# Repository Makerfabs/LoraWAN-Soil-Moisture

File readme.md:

# LoraWAN Soil Moisture

```c++
/*
Version:		V1.2
Author:			Vincent
Create Date:	2022/12/15
Note:
	2022/12/30	V1.2	:Update readme
	2022/12/16 	V1.1	:Fix adc3 read error.
*/
```

[toc]

# Makerfabs

[Makerfabs home page](https://www.makerfabs.com/)

[Makerfabs Wiki](https://wiki.makerfabs.com/)

# LoraWAN Soil Moisture
## Intruduce

Product Link ：[LoRaWAN Temperature/ Humidity/ Soil Moisture Sensor](https://www.makerfabs.com/lorawan-temperatur-humidity-soil-moisture-sensor.html) 

Wiki Link : [LoRaWAN Temperature/ Humidity Soil Moisture Sensor](https://wiki.makerfabs.com/LoRaWAN_Temperature_Humidity_Soil_Moisture_Sensor.html) 

This module monitor soil moisture via capacitive method, with waterproof coating, it avoids the corrosion problem that usually happens on cheap resistor-mode soil moisture sensor. There is also onboard AHT10 -air temperature/ humidity sensor, to monitor air status, proper for usage in the greenhouse. This module uses 3x AAA battery as power, with sleep current of 26uA and working current of 4mA, the average working time can be more than 1 year. (with 1-hour message interval, Class A ).

## Feature

- LoRaWAN Nodes, RA08H
- Soil Moisture Measurement based on capacitive Testing
- Low power: 7.1uA when sleeping/4mA in message sending turn around
- Onboard AHT10 sensor to monitor air temperature and air humidity
- Onboard Battery Voltage Measurement
- Full Open Source- all hardware and software open at GitHub
- Compatible with Arduino
- Supply power voltage: 4.7~3.5V

### Front:

### Back:

# Code

## Compiler Options

**If you have any questions，such as how to install the development board, how to download the code, how to install the library. Please refer to :[Makerfabs_FAQ](https://github.com/Makerfabs/Makerfabs_FAQ)**

- Open code with Arduino IDE
- Set Lorawan config in code.
- Upload codes, select "Arduino Pro or Pro Mini" and "3.3V 8MHz"

## Uploader

There is no USB socket or integrated serial port chip on some modules. But there are serial ports: VCC, GND, RX, TX, DTR. 

There are two ways to connect a serial port.

### MakerFabs CP2104 USB2UART

Product link : [CP2104 USB2UART](https://www.makerfabs.com/cp2104-usb-to-serial-converter.html)

This CP2104 USB to Serial Converter is super tiny, a highly-integrated USB-to-UART Bridge Controller providing a simple solution for updating and programming.

The serial port module has the same pin position as the makerfabs module with no USB port. So just plug it into the hole.

The usage of usb cable is the same after that.

### CP2102 MODULES USB TO TTL

There are many common USB serial port modules on the market, which are basically connected in a common way.

| Makerfabs | USB To TTL |
| --------- | ---------- |
| VCC       | 3.3V       |
| GND       | GND        |
| RX        | TXD        |
| TX        | RXD        |

## Testing file for manufacture

**moisture_test.ino**

This is a test demo. You can check all sensor, button, led and Lorawan.

Change Lorawan config to yourself.

```c++
//config.h

#define DEVEUI "YOUR_DEVEUI"
#define APPEUI "YOUR_APPEUI"
#define APPKEY "YOUR_APPKEY"

```

When hold on button, will send lorawan message to TTN.

```c++

```

## Firmware Frame

**mositure_lorawan**

This routine is expected to run on 3 AAA batteries for a year (once per hour).

Hibernation current 26ua, normal working current 4.7ma, peak emission 8.7ma.

The register is used to read the soil ADC and the battery voltage ADC. 

~~*There is a bug in the battery voltage ADC reading at present and it is being modified.*~~

Change Lorawan config to yourself.

Set sleep time, every watchdog sleep cycle nearly 8.5 s.

```c++
//Almost 1 hours
#define SLEEP_CYCLE 450
```

Lorawan sends data in the following ways:

```c++
    String temp = "AT+DTRX=1,2,8,";

    char data_str[80];
    sprintf(data_str, "%02x%02x%02x%02x", 
            (int)temperature, (int)humidity, soil_percent, bat_vol);
    temp = temp + data_str;
```

The corresponding parsing function for the thing network is as follows:

```javascript
function decodeUplink(input) {
  
  var temp = input.bytes[0]
  var humi = input.bytes[1]
  var adc = input.bytes[2]*256+input.bytes[3]
  var bat = input.bytes[4]/10
  var num = input.bytes[5] * 100 + input.bytes[6] 
  
  return {
    data:{
    //adc,
    //temp,
    //humi,
    //bat,
    //num,
    field1:adc,
    field2:temp,
    field3:humi,
    field4:bat,
    field5:num,
    },
    
  };
  
```

## Example

### 328p_at

Example for AT command test.

### adc_sleep

Tests whether ADC reads normally after MCU sleeps.

# Case

3D print case

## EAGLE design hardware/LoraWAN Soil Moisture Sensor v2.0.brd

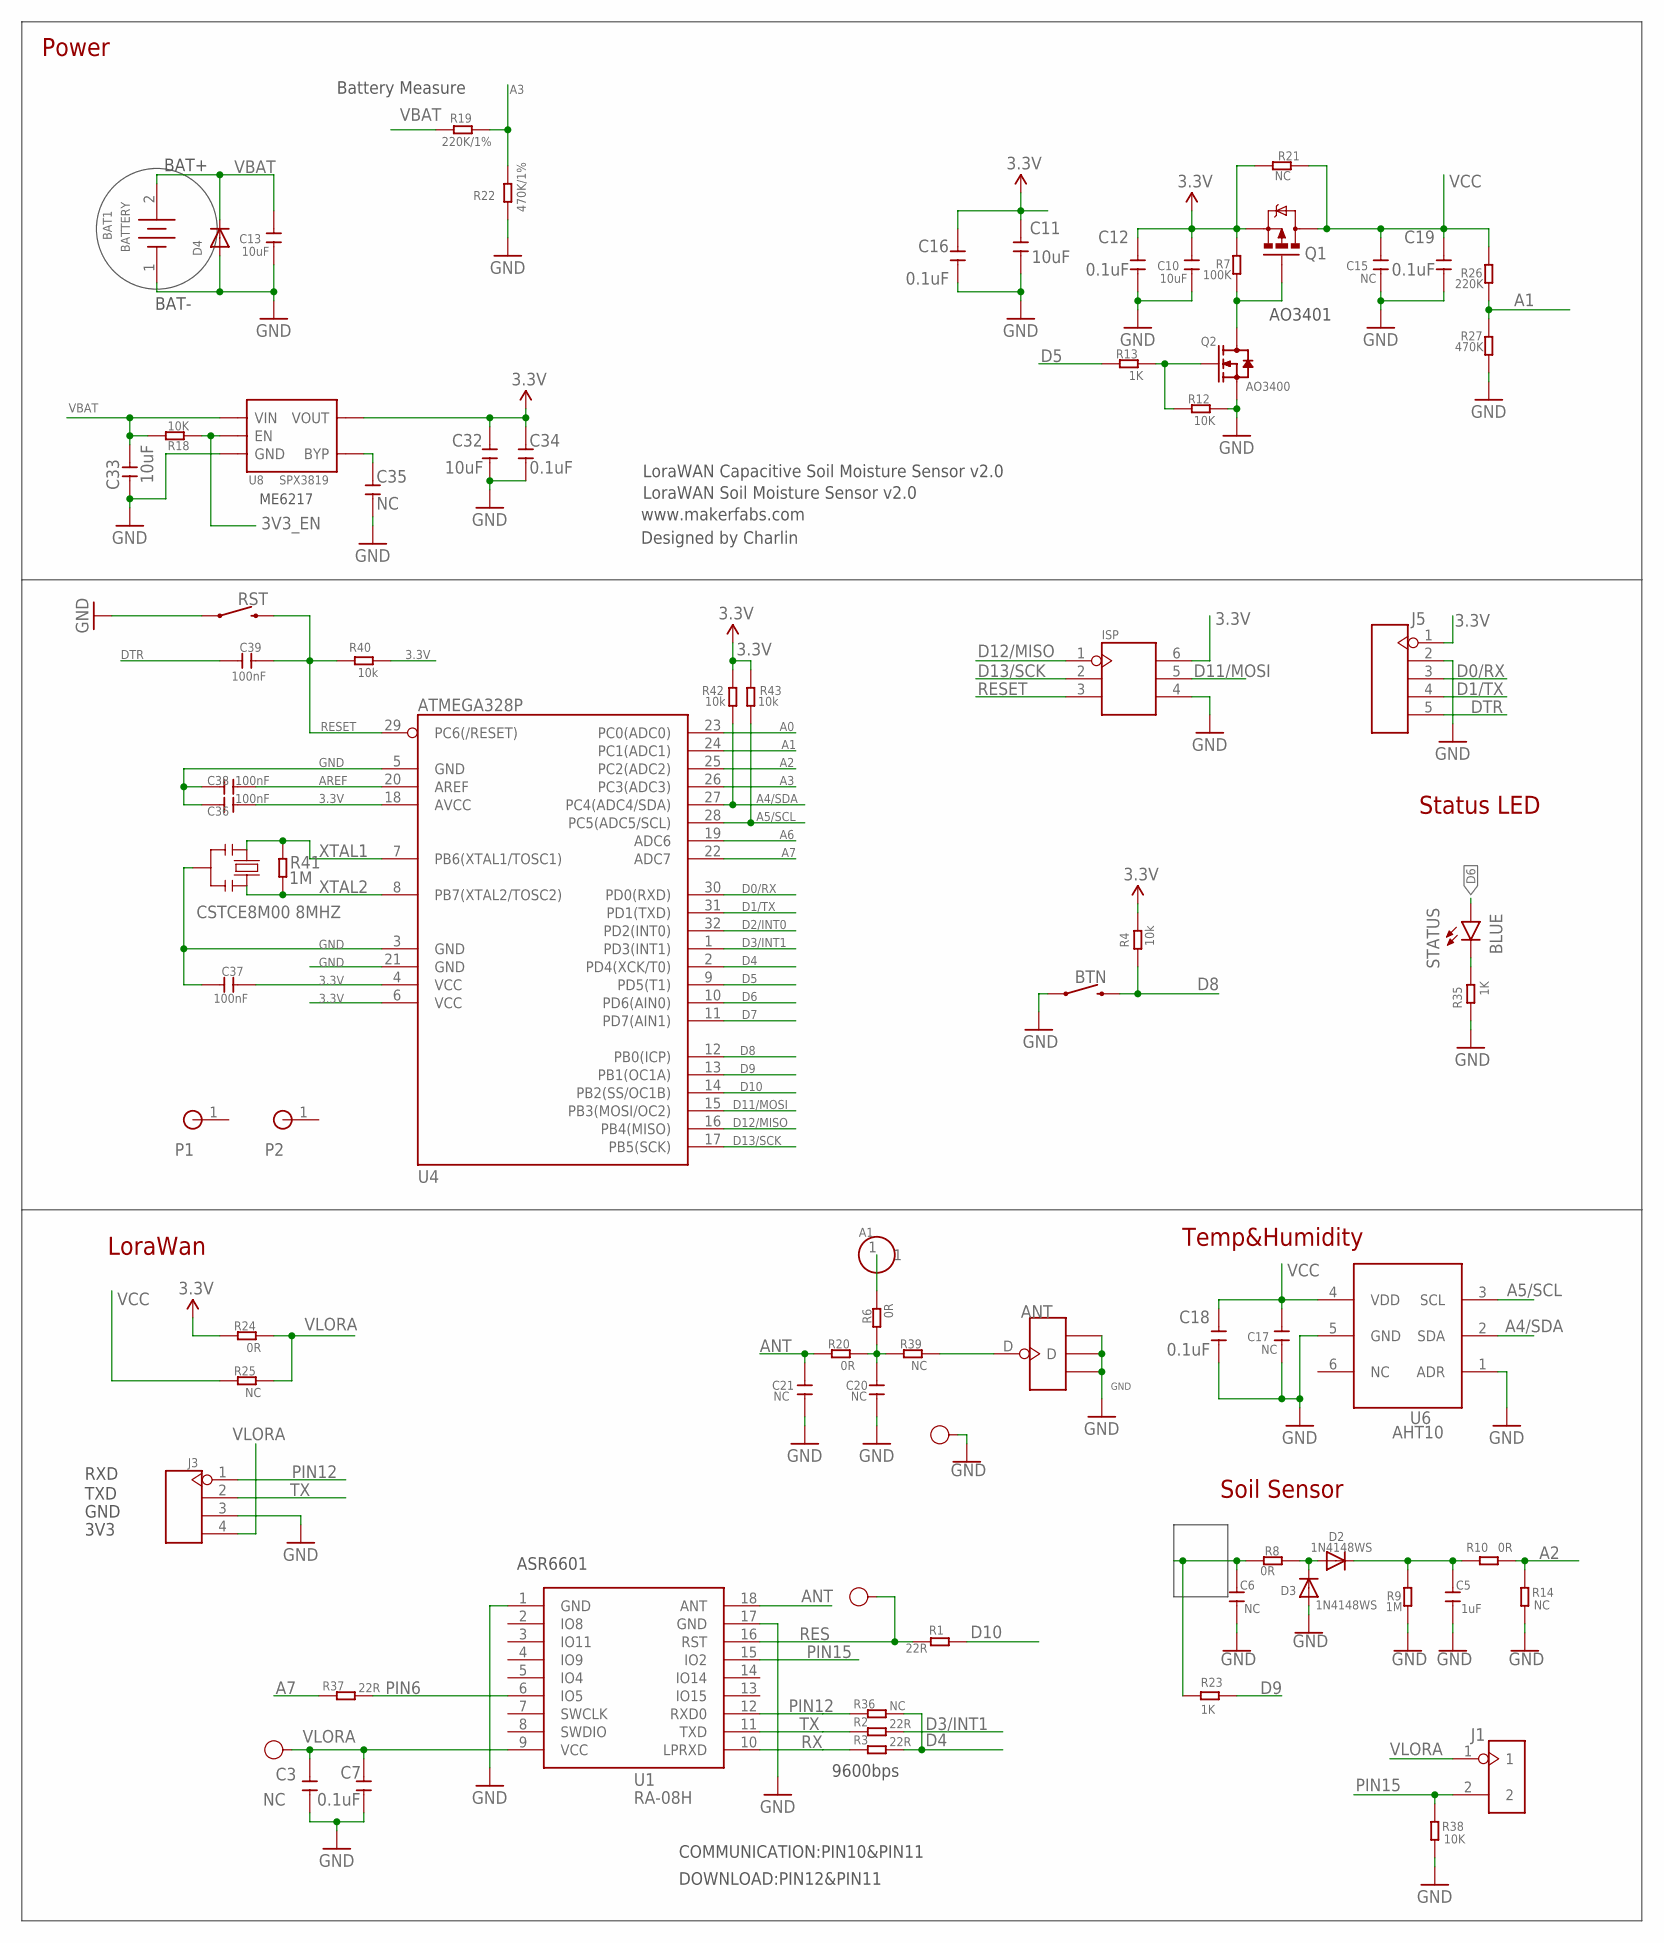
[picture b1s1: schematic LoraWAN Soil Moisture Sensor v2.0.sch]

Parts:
3V3: TEST-POINT'4545'; TP-D45MIL; PARTNO DNP
A1: HEADER-1P-50; 1P-100/50MIL
ANT: ANTENNA-U-FL; 4P-U-FL
BAT1: BATTERY
BTN: MOMENTARY-SWITCH-SPST-SMD-6.0X3.5MM; TACTILE_SWITCH_SMD_6.0X3.5MM
C3, C15, C17, C20, C21, C35: NC; 0603
C5: 1uF; DISCRETE_C0603
C6: NC; DISCRETE_C0603
C7, C12, C16, C18, C19, C34: 0.1uF; 0603
C10, C11, C13, C32, C33: 10uF; 0603
C36, C37, C38, C39: 100nF; 0603
D2, D3: 1N4148WS; SOD-323F
D4: DIODESOD-323F; SOD-323F
GND: TEST-POINT'4545'; TP-D45MIL
ISP: HEADER-2X3P-SMD; 2X3P-2.54-SMD
J1: HEADER-2P-2.0; 2P-2.0
J3: HEADER-4P-60/35MILROUND; 4P-65/35ROUND
J5: HEADER-5P-2.54; 5P-2.54
P1, P2: HOLE-P1-2.2; MTGNP1-220-1MM
Q1: MOSFET-PCHANNEL; SOT23-3
Q2: AO3400; DISCRETE_SOT23
R1, R2, R3, R37: 22R; R0603
R4, R40, R42, R43: 10k; R0603
R6, R8, R10, R20, R24: 0R; R0603
R7: 100K; R0603
R9, R41: 1M; R0603
R12, R18, R38: 10K; R0603
R13, R23, R35: 1K; R0603
R14, R21, R25, R36, R39: NC; R0603
R19: 220K/1%; R0603
R22: 470K/1%; R0603
R26: 220K; R0603
R27: 470K; R0603
RES: TEST-POINT'4545'; TP-D45MIL; PARTNO DNP
RST: MOMENTARY-SWITCH-SPST-SMD-6.0X3.5MM; TACTILE_SWITCH_SMD_6.0X3.5MM
STATUS: BLUE; LED-0603
U1: RA-08H
U4: ATMEGA328P; TQFP32
U6: AHT10; SMD6-127P-400L500W
U8: SPX3819; SOT23-5
Y1: CSTCE8M00 8MHZ; RESONATOR

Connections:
3.3V: C10.2, C11.2, C12.2, C16.2, C32.2, C34.2, C36.2, C37.2, ISP.6, J5.1, Q1.2 (S), R4.1, R7.2, R21.2, R24.2, R40.1, R42.1, R43.1, U4.4 (VCC), U4.6 (VCC), U4.18 (AVCC), U8.5 (VOUT)
3V3_EN: R18.2, U8.3 (EN)
A0: U4.23 (PC0(ADC0))
A1: R26.1, R27.2, U4.24 (PC1(ADC1))
A2: R10.2, R14.1, U4.25 (PC2(ADC2))
A3: R19.1, R22.2, U4.26 (PC3(ADC3))
A4/SDA: R42.2, U4.27 (PC4(ADC4/SDA)), U6.2 (SDA)
A5/SCL: R43.2, U4.28 (PC5(ADC5/SCL)), U6.3 (SCL)
A6: U4.19 (ADC6)
A7: R37.1, U4.22 (ADC7)
ANT: C21.2, R20.2, U1.18 (ANT)
AREF: C38.2, U4.20 (AREF)
D0/RX: J5.3, U4.30 (PD0(RXD))
D1/TX: J5.4, U4.31 (PD1(TXD))
D2/INT0: U4.32 (PD2(INT0))
D3/INT1: R2.2, U4.1 (PD3(INT1))
D4: R3.2, R36.2, U4.2 (PD4(XCK/T0))
D5: R13.2, U4.9 (PD5(T1))
D6: STATUS.A, U4.10 (PD6(AIN0))
D7: U4.11 (PD7(AIN1))
D8: BTN.2, R4.2, U4.12 (PB0(ICP))
D9: R23.2, U4.13 (PB1(OC1A))
D10: R1.2, U4.14 (PB2(SS/OC1B))
D11/MOSI: ISP.5, U4.15 (PB3(MOSI/OC2))
D12/MISO: ISP.1, U4.16 (PB4(MISO))
D13/SCK: ISP.2, U4.17 (PB5(SCK))
DTR: C39.1, J5.5
GND: ANT.GND1, ANT.GND2, ANT.GND3, BAT1.1, BTN.1, C3.1, C5.1, C6.1, C7.1, C10.1, C11.1, C12.1, C13.1, C15.1, C16.1, C17.1, C18.1, C19.1, C20.1, C21.1, C32.1, C33.1, C34.1, C35.1, C36.1, C37.1, C38.1, D3.A, D4.A, GND.T, ISP.4, J3.3, J5.2, Q2.2 (S), R9.1, R12.1, R14.2, R22.1, R27.1, R35.2, R38.2, RST.1, U1.1 (GND), U1.17 (GND), U4.3 (GND), U4.5 (GND), U4.21 (GND), U6.1 (ADR), U6.5 (GND), U8.2 (GND), Y1.2
unnamed: ANT.D, R39.1
unnamed: C6.2, R8.1, R23.1
unnamed: A1.1, R6.1
unnamed: Q1.1 (G), Q2.3 (D), R7.1
unnamed: D2.A, D3.C, R8.2
unnamed: Q2.1 (G), R12.2, R13.1
unnamed: C5.2, D2.C, R9.2, R10.1
unnamed: C20.2, R6.2, R20.1, R39.2
unnamed: C35.2, U8.4 (BYP)
unnamed: R35.1, STATUS.C
PIN6: R37.2, U1.6 (IO5)
PIN12: J3.1, R36.1, U1.12 (RXD0)
PIN15: J1.2, R38.1, U1.15 (IO2)
RES: R1.1, RES.T, U1.16 (RST)
RESET: C39.2, ISP.3, R40.2, RST.2, U4.29 (PC6(/RESET))
RX: R3.1, U1.10 (LPRXD)
TX: J3.2, R2.1, U1.11 (TXD)
VBAT: BAT1.2, C13.2, C33.2, D4.C, R18.1, R19.2, U8.1 (VIN)
VCC: C15.2, C17.2, C18.2, C19.2, Q1.3 (D), R21.1, R25.2, R26.2, U6.4 (VDD)
VLORA: 3V3.T, C3.2, C7.2, J1.1, J3.4, R24.1, R25.1, U1.9 (VCC)
XTAL1: R41.2, U4.7 (PB6(XTAL1/TOSC1)), Y1.1
XTAL2: R41.1, U4.8 (PB7(XTAL2/TOSC2)), Y1.3

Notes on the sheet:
LoraWAN Soil Moisture Sensor v2.0
www.makerfabs.com
LoraWAN Capacitive Soil Moisture Sensor v2.0
Designed by Charlin
BAT+
BAT-
AO3401
RXD
TXD
GND
3V3
ME6217
Battery Measure
Status LED
Temp&Humidity
Soil Sensor
LoraWan
Power
ASR6601
COMMUNICATION:PIN10&PIN11
DOWNLOAD:PIN12&PIN11
9600bps

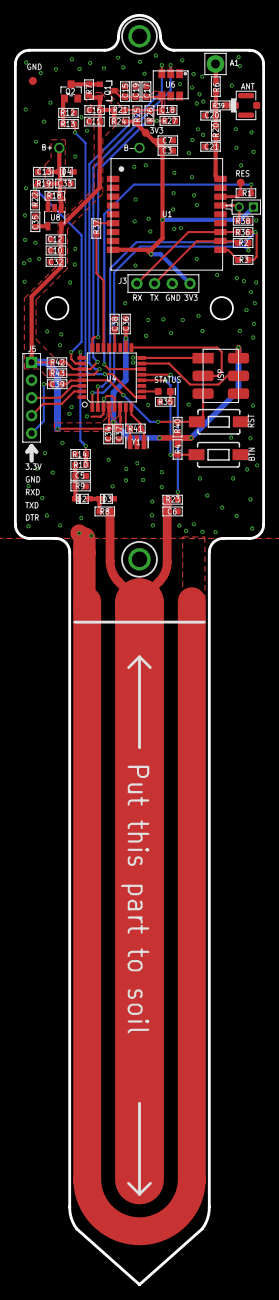
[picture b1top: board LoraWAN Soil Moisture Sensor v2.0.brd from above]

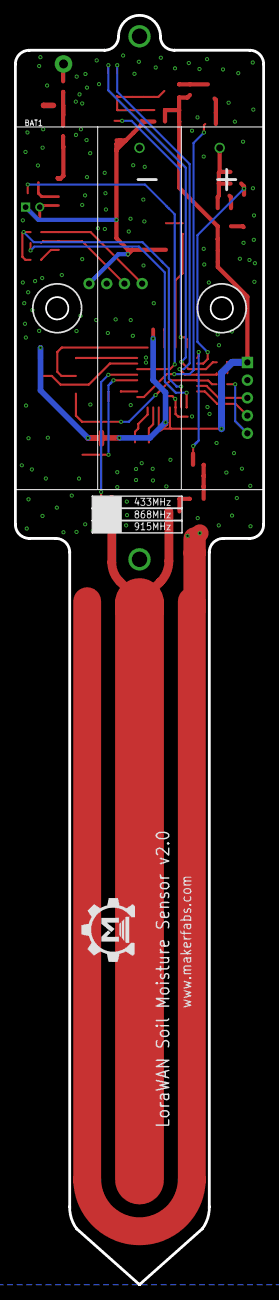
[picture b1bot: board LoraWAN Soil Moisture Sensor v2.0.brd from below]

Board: 2 copper layers, 35.6 x 182.0 mm, 80 parts (2 on the bottom side), 46 nets.

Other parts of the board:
U$7: MAKERFABS_0.3

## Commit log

2022-12-13 Create Project
2022-12-14 Fix bug
2022-12-15 Edit readme
2022-12-15 Change File Name
2022-12-16 Fix adc read bug.
2022-12-30 Add 3dp case.
2023-01-04 Add tx count, fix test code bug.
2023-01-04 Change code logic
2023-01-09 RA08H firmware and tool
2023-07-25 Change upload value
2023-12-19 Update moisture_lorawan.ino
    Soil values between 560 and 740 need two bytes.
2024-09-14 add demo

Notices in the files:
parts and their libraries:
User-Submitted: Licensing: Creative Commons ShareAlike 4.0 International - https://creativecommons.org/licenses/by-sa/4.0
